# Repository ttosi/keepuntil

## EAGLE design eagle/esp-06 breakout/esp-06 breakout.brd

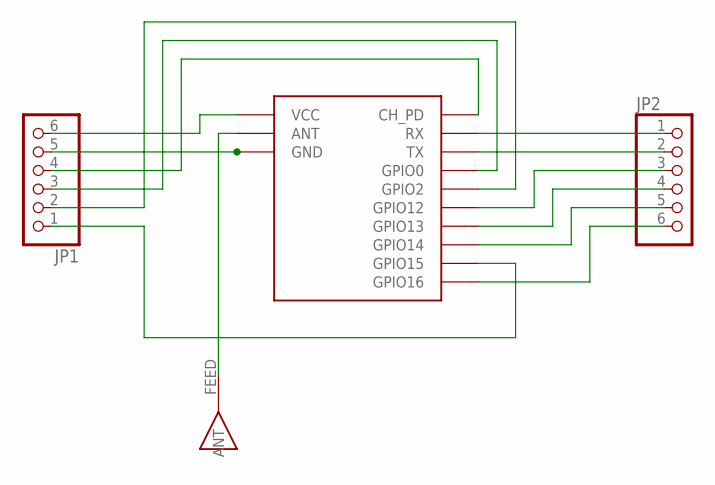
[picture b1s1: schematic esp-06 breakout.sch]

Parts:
JP1, JP2: PINHD-1X6; 1X06
U$1: ESP06
U$2: ANT; ANTENNA-CERAMIC

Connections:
unnamed: JP1.6, U$1.VCC
unnamed: JP1.5, U$1.GND, U$1.GND1 (GND2), U$1.GND2 (GND3), U$1.GND3 (GND4), U$1.GND4 (GND5), U$1.GND5 (GND6), U$1.GND6 (GND7), U$1.GND7 (GND8)
unnamed: JP1.4, U$1.CH_PD
unnamed: JP2.1, U$1.RX
unnamed: JP2.2, U$1.TX
unnamed: JP1.3, U$1.GPIO0
unnamed: JP1.2, U$1.GPIO2
unnamed: JP2.3, U$1.GPIO12
unnamed: JP2.4, U$1.GPIO13
unnamed: JP2.5, U$1.GPIO14
unnamed: JP1.1, U$1.GPIO15
unnamed: JP2.6, U$1.GPIO16
unnamed: U$1.ANT, U$2.FEED

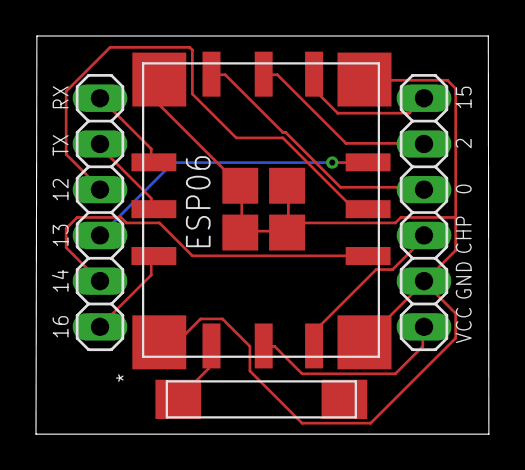
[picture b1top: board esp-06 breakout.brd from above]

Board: 2 copper layers, 25.2 x 22.1 mm, 4 parts (0 on the bottom side), 13 nets.

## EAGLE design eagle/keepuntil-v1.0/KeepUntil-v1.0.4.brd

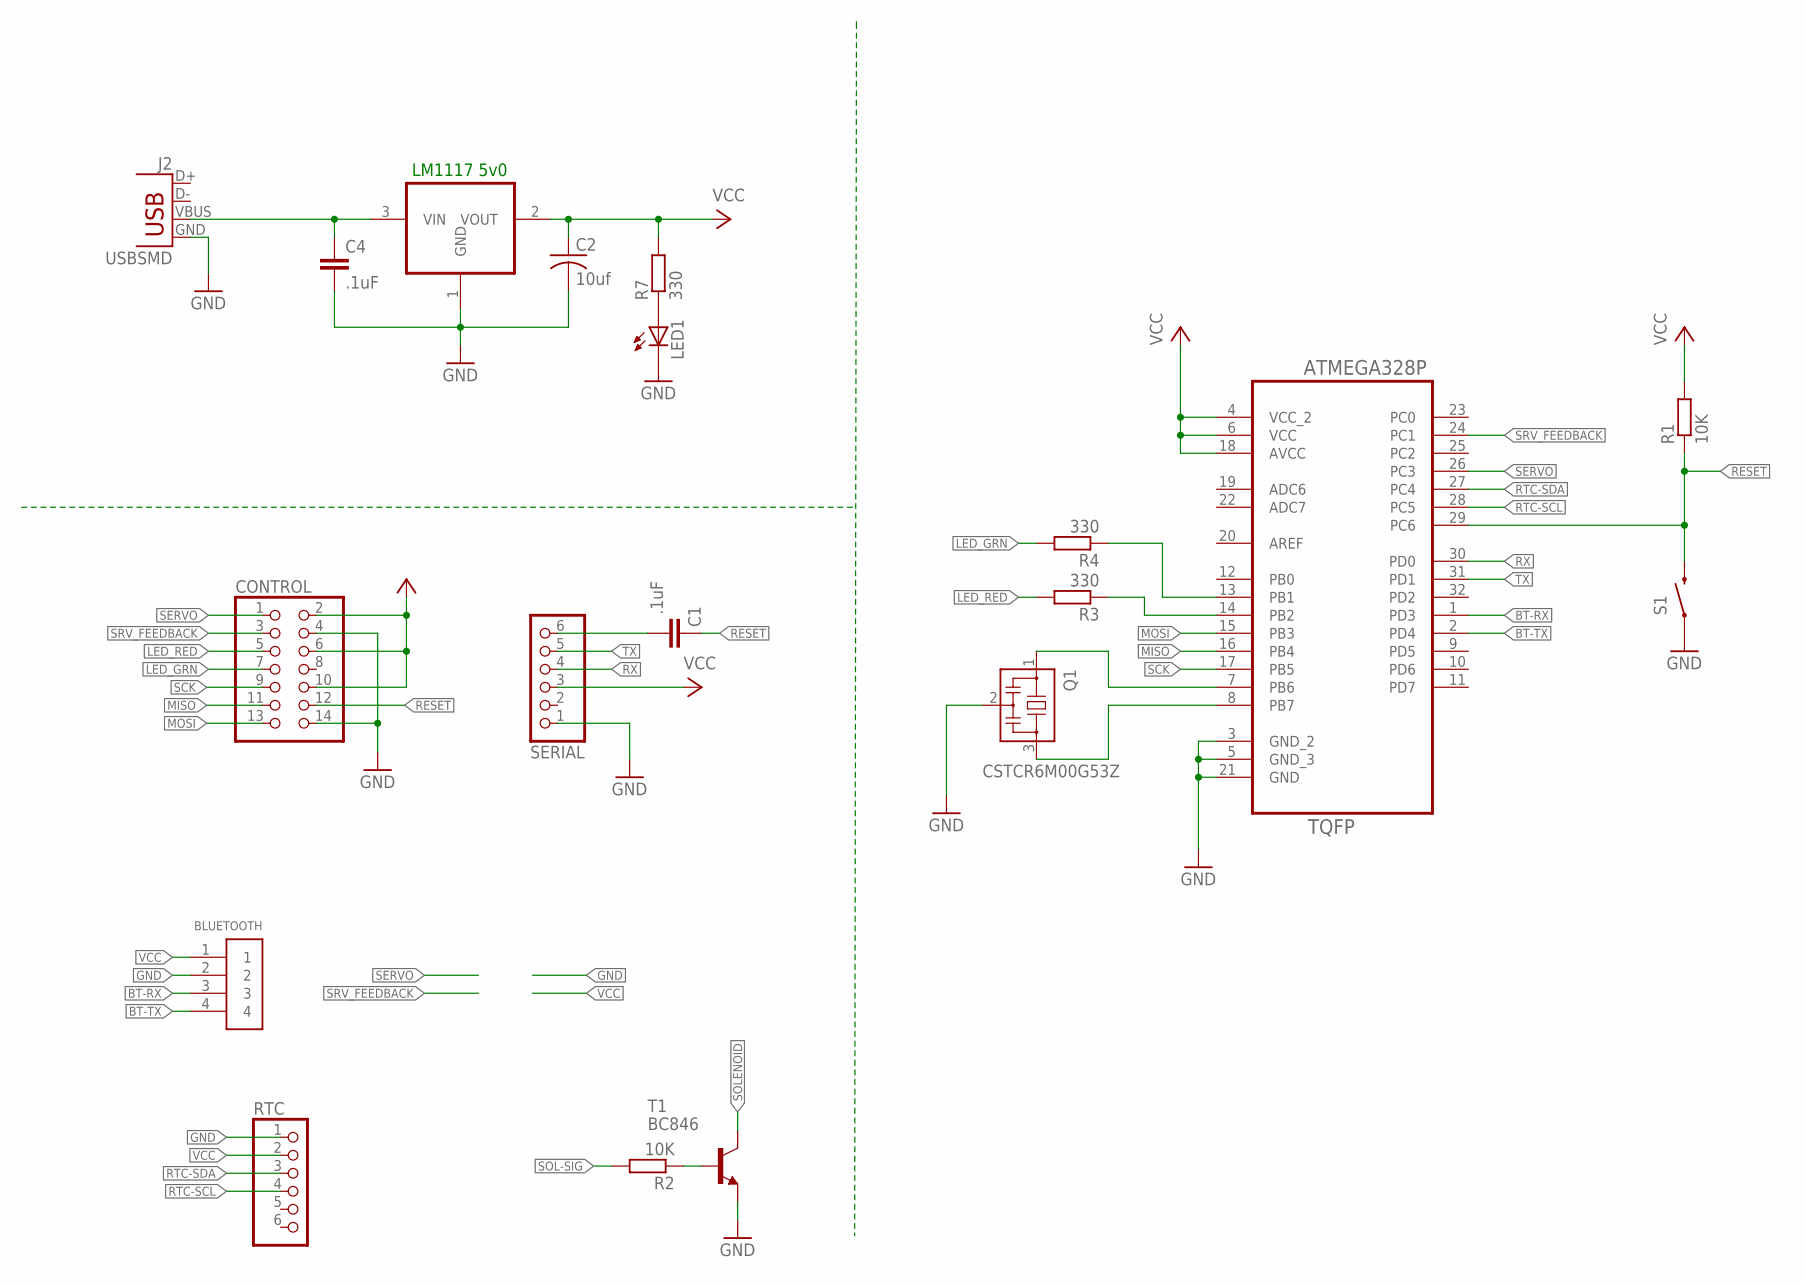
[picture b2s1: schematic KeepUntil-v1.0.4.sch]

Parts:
BLUETOOTH: 1X4-CLEANBIG; 1X04-CLEANBIG
C1, C4: .1uF; C0805
C2: 10uf; C1206
CONTROL: PINHD-2X7; 2X07
IC2: REG1117; SOT223; MPN LM1117 3v3
J2: USBSMD; USB-MINIB
LED1: LEDSMT1206; 1206
Q1: CSTCR6M00G53Z; CSTCR6M
R1, R2: 10K; R0805
R3, R4, R7: 330; R0805
RTC: PINHD-1X6CLEAN; 1X06-CLEAN
S1: SWITCH-MOMENTARY-2SMD-1101NE; TACTILE-SWITCH-1101NE
SERIAL: PINHD-1X6CLEAN; 1X06-CLEAN
T1: BC846; SOT23
U1: ATMEGA328P-AU; QFP80P900X900X120-32N

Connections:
BT-RX: BLUETOOTH.3, U1.1 (PD3)
BT-TX: BLUETOOTH.4, U1.2 (PD4)
GND: BLUETOOTH.2, C2.2, C4.2, CONTROL.4, CONTROL.14, IC2.1 (GND), J2.GND, LED1.C, Q1.2, RTC.1, S1.1, SERIAL.1, T1.2 (E), U1.3 (GND_2), U1.5 (GND_3), U1.21 (GND)
LED_GRN: CONTROL.7, R4.2
LED_RED: CONTROL.5, R3.2
MISO: CONTROL.11, U1.16 (PB4)
MOSI: CONTROL.13, U1.15 (PB3)
unnamed: Q1.1, U1.7 (PB6)
unnamed: Q1.3, U1.8 (PB7)
unnamed: R2.1, T1.1 (B)
unnamed: C4.1, IC2.3 (VIN), J2.VBUS
unnamed: LED1.A, R7.1
unnamed: R3.1, U1.14 (PB2)
unnamed: R4.1, U1.13 (PB1)
unnamed: C1.2, SERIAL.6
RESET: C1.1, CONTROL.12, R1.1, S1.2, U1.29 (PC6)
RTC-SCL: RTC.4, U1.28 (PC5)
RTC-SDA: RTC.3, U1.27 (PC4)
RX: SERIAL.4, U1.30 (PD0)
SCK: CONTROL.9, U1.17 (PB5)
SERVO: CONTROL.1, U1.26 (PC3)
SOL-SIG: R2.2
SOLENOID: T1.3 (C)
SRV_FEEDBACK: CONTROL.3, U1.24 (PC1)
TX: SERIAL.5, U1.31 (PD1)
VCC: BLUETOOTH.1, C2.1, CONTROL.2, CONTROL.6, CONTROL.10, IC2.2 (VOUT), R1.2, R7.2, RTC.2, SERIAL.3, U1.4 (VCC_2), U1.6 (VCC), U1.18 (AVCC)

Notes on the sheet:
LM1117 5v0

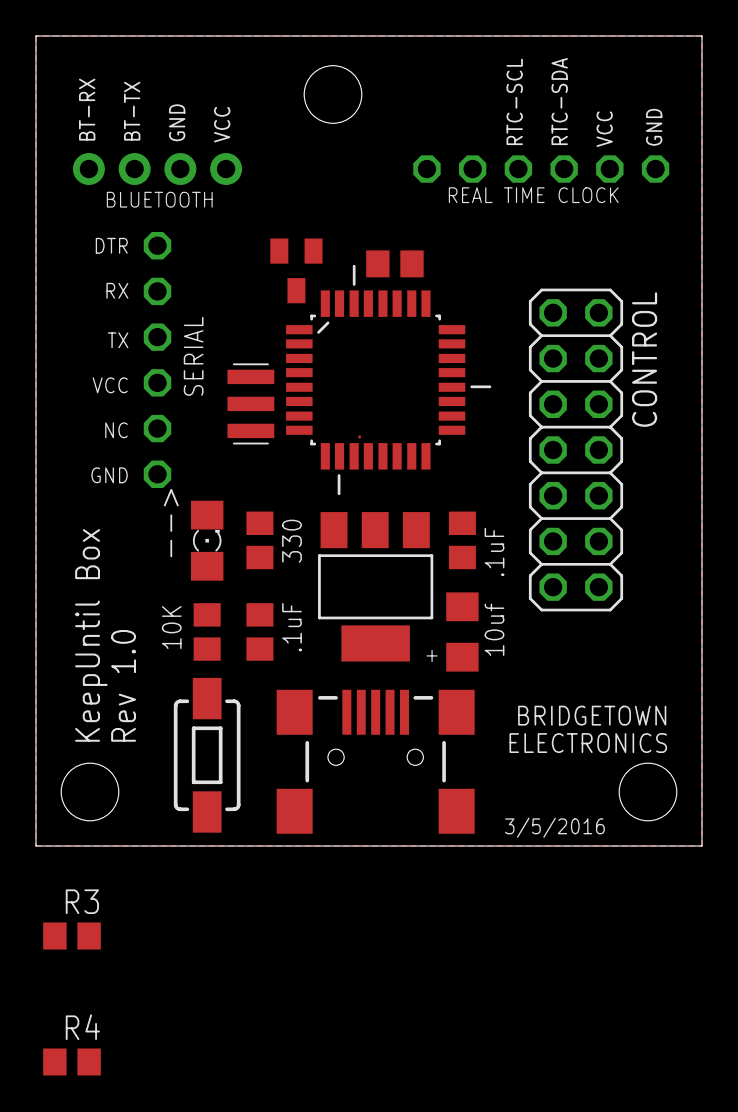
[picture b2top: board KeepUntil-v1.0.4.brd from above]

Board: 2 copper layers, 37.0 x 45.0 mm, 19 parts (0 on the bottom side), 24 nets.

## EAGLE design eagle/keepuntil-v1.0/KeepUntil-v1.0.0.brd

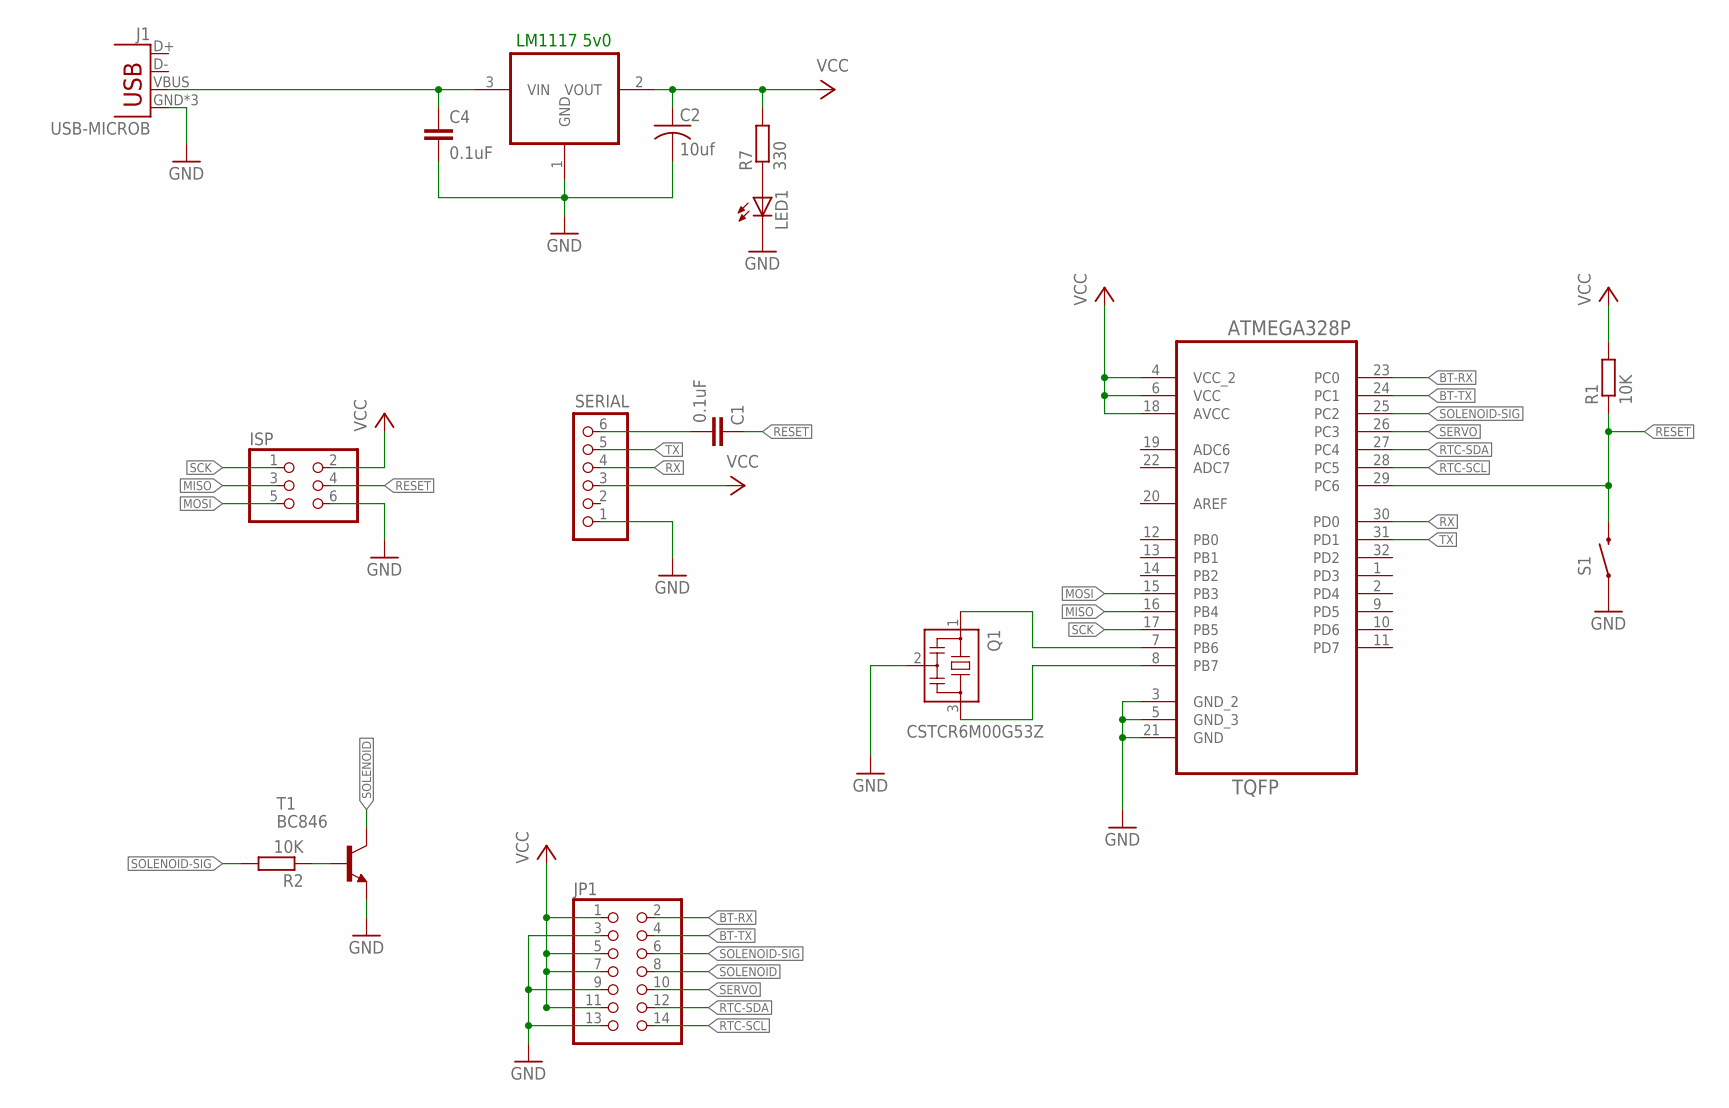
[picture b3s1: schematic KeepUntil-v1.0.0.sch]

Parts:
C1, C4: 0.1uF; C0805
C2: 10uf; C1206
IC2: REG1117; SOT223; MPN LM1117 3v3
ISP: PINHD-2X3; 2X03
J1: USB-MICROB
JP1: PINHD-2X7; 2X07
LED1: LEDSMT1206; 1206
Q1: CSTCR6M00G53Z; CSTCR6M
R1, R2: 10K; R0805
R7: 330; R0805
S1: SWITCH-MOMENTARY-2SMD-1101NE; TACTILE-SWITCH-1101NE
SERIAL: PINHD-1X6; 1X06
T1: BC846; SOT23
U1: ATMEGA328P-AU; QFP80P900X900X120-32N

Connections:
BT-RX: JP1.2, U1.23 (PC0)
BT-TX: JP1.4, U1.24 (PC1)
GND: C2.2, C4.2, IC2.1 (GND), ISP.6, J1.GND, J1.MT1 (GND), J1.MT2 (GND), JP1.3, JP1.9, JP1.13, LED1.C, Q1.2, S1.1, SERIAL.1, T1.2 (E), U1.3 (GND_2), U1.5 (GND_3), U1.21 (GND)
MISO: ISP.3, U1.16 (PB4)
MOSI: ISP.5, U1.15 (PB3)
unnamed: Q1.1, U1.7 (PB6)
unnamed: Q1.3, U1.8 (PB7)
unnamed: R2.1, T1.1 (B)
unnamed: C4.1, IC2.3 (VIN), J1.VBUS
unnamed: LED1.A, R7.1
unnamed: C1.2, SERIAL.6
RESET: C1.1, ISP.4, R1.1, S1.2, U1.29 (PC6)
RTC-SCL: JP1.14, U1.28 (PC5)
RTC-SDA: JP1.12, U1.27 (PC4)
RX: SERIAL.4, U1.30 (PD0)
SCK: ISP.1, U1.17 (PB5)
SERVO: JP1.10, U1.26 (PC3)
SOLENOID: JP1.8, T1.3 (C)
SOLENOID-SIG: JP1.6, R2.2, U1.25 (PC2)
TX: SERIAL.5, U1.31 (PD1)
VCC: C2.1, IC2.2 (VOUT), ISP.2, JP1.1, JP1.5, JP1.7, JP1.11, R1.2, R7.2, SERIAL.3, U1.4 (VCC_2), U1.6 (VCC), U1.18 (AVCC)

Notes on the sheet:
LM1117 5v0

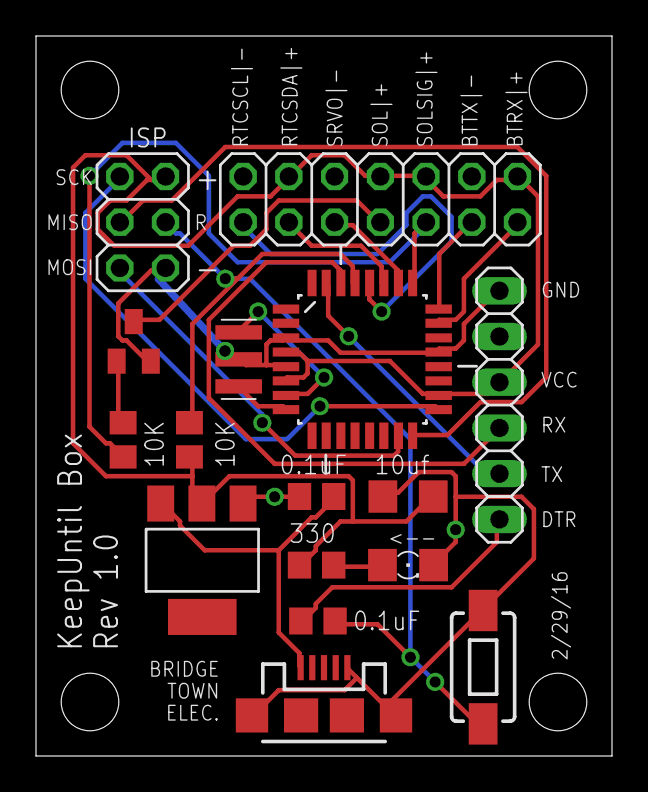
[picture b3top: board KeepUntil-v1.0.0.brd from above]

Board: 2 copper layers, 32.0 x 40.0 mm, 16 parts (0 on the bottom side), 21 nets.

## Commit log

2016-01-22 Test commit
2016-01-22 test commit 2
2016-01-22 update open at datetime string to lcd
2016-01-23 add comments
2016-01-24 Latest version
2016-01-26 add eagle files
2016-01-26 remove __vm directory take 2
2016-01-26 schematic work
2016-01-26 remove visual micro specific file
2016-01-27 remove unnecessary eagle file
2016-01-27 update schematic
2016-01-27 schematic cleanup
2016-02-01 board layout
2016-02-02 add servo dim reference
2016-02-09 pin header updates in schematic
2016-02-15 schematic
2016-02-17 schematic & board
2016-02-29 add phonegap skeleton
2016-02-29 schematic cleanup and board
2016-02-29 board
2016-03-02 board final rev1.0
2016-03-03 new board layout
2016-03-05 testing phonegap
2016-03-05 testing phonegap bluetooth
2016-03-05 add bluetooth plugin
2016-03-05 debug
2016-03-05 remove plugins and hooks dir
2016-03-07 layout framework for mobile app
2016-03-07 add missing libs
2016-03-08 add icon, move wait dialog to utils
2016-03-10 mobile app initial testing
2016-03-13 mobile app dev
2016-03-14 mobile app work
2016-03-17 get oat and rtc and display in gui
2016-03-21 working oat and rtc set amd get
2016-03-23 major mobile app work
2016-03-28 working pg app, start v2 board
2016-04-11 firmware improvements
2016-04-13 board rev. b
2016-05-09 board rev b tweaks
2016-06-24 test

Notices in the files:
parts and their libraries:
SparkFun-Electromechanical: Licensing: Creative Commons ShareAlike 4.0 International - https://creativecommons.org/licenses/by-sa/4.0
